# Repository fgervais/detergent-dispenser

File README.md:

# Detergent Dispenser

HE laundry detergent is quite concentrated and front loading washing machines
use really little water. With those two factors put together, it's really easy
to put too much detergent and so soap will be left even after the rinse cycle.

This project aim to automate the dispensing of a precise amount of detergent.

## Board

## Assembled Unit

After holding the button for 1 seconds, the pump will dispense 7.5ml of
detergent. This has been empirically determined to be the required amount
for a small load on our dishwasher using our usual soap.

## Installed

The pump feeds directly from the bottle.

### Resource Efficiency

The bottle in this picture is rated for 44 loads but with the proper quantity determined for our specific case along with precise dispensing, we will get over 250 loads from this bottle.

(272 small loads of 7.5ml)

## Control App (Blynk)

The app shows when a dispense occurred and keep a global count since last
manual reset. It is also possible to start a dispense from the app.

All controls are locked by default and need to get unlocked through the
lock/unlock button. Once unlocked, only a single action is allowed before
controls are locked again automatically. This is to prevent unwanted counter reset or dispense.

## Next Steps

A couple improvements could be done to this project.

1. The output of the dispenser could be permanently mounted to the washing
machine soap compartment.

2. In normal mode, the esp32 uses quite a lot of power and this translates to
a power regulator hovering just under 70C in normal operation. As the device
does nothing most of the time, power management could be added so the regulator
doesn't have to dissipate that much power.

3. The ground/power doesn't seem to be so stable on the board as touching the
pins can sometime trigger a button press or a glitch on the pump sync signal.
This doesn't seem to be too much of an issue when the device is assembled in
the case.

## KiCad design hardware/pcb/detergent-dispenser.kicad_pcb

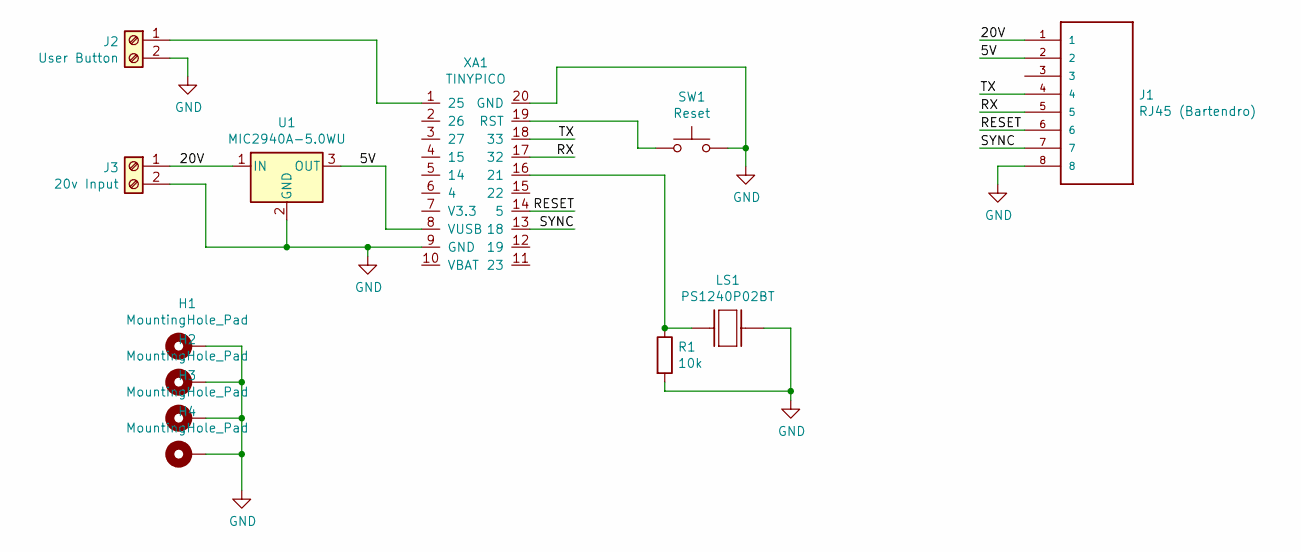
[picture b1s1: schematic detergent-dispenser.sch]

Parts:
H1, H2, H3, H4: MountingHole_Pad; MountingHole_2.7mm_M2.5_Pad
J1: RJ45 (Bartendro); AMPHENOL_RJHSE-5080
J2: User Button; TE_1546215-2
J3: 20v Input; TE_1546215-2
LS1: PS1240P02BT; XDCR_PS1240P02BT
R1: 10k; C_0603_1608Metric_Pad1.05x0.95mm_HandSolder
SW1: Reset; SW_SPST_TL3342
U1: MIC2940A-5.0WU; TO-263-3_TabPin2
XA1: TINYPICO

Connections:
/5V: J1.2, U1.3 (OUT), XA1.8 (VUSB)
/20V: J1.1, J3.1, U1.1 (IN)
/RESET: J1.6, XA1.14 (5)
/RX: J1.5, XA1.17 (32)
/SYNC: J1.7, XA1.13 (18)
/TX: J1.4, XA1.18 (33)
GND: H1.1, H2.1, H3.1, H4.1, J1.8, J2.2, J3.2, LS1.2, R1.2, SW1.2, U1.2 (GND), XA1.9 (GND), XA1.20 (GND)
unnamed: J2.1, XA1.1 (25)
unnamed: LS1.1, R1.1, XA1.16 (21)
unnamed: SW1.1, XA1.19 (RST)

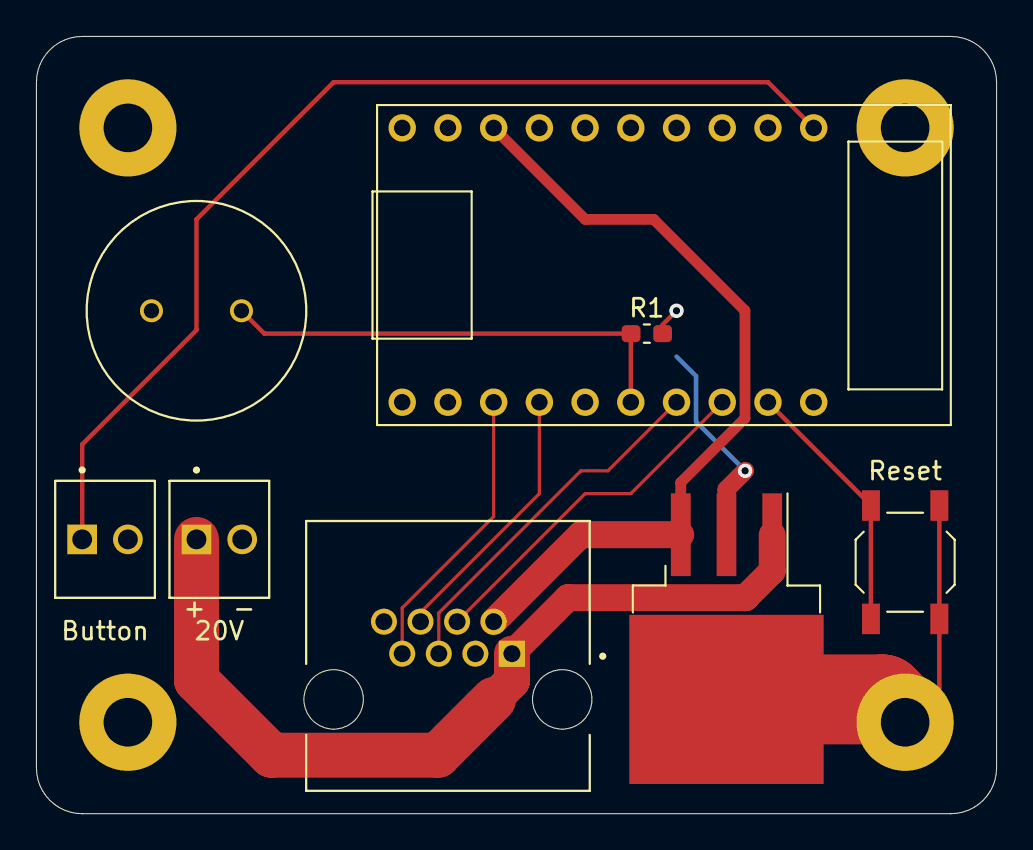
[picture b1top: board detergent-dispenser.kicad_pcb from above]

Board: 2 copper layers, 53.3 x 43.2 mm, 12 parts (0 on the bottom side), 10 nets.

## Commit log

2020-09-07 PCB rev 0
2020-09-08 Export rev 0 schematic as pdf
2020-09-08 Got the Bartendro reset and sync pin going
2020-10-12 Send the pump discovery token and add button
2020-10-12 Add initial README
2020-10-12 Detect when Bartendro is ready
2020-10-12 Add a note to PCB about 5v protection
2020-10-13 Add button IRQ
2020-10-13 Print help on button press
2020-10-15 Enter text mode in every cases
2020-11-19 Set led_done on button press
2020-11-21 Dispense outside of interrupt context
2020-11-23 Add lib-python submodule
2020-11-23 Add control over a blynk button
2020-12-10 Enable WebREPL
2020-12-10 Add upydev
2020-12-13 Add lock button handling
2020-12-13 Remove commented out code
2020-12-13 Pump only a little
2020-12-13 Use SSL
2020-12-13 Format main.py with black
2020-12-13 Remove SSL connection through proxy
2020-12-13 Sync dispense count
2020-12-13 Automatically lock controls
2020-12-13 Add counter handling
2020-12-13 Add upydev config to ignored files
2020-12-21 Use blynklib_ssl.SslConnection
2020-12-21 Early connect to wifi
    Allows connecting to the wrepl earlier.
2020-12-21 Do not use leds
2020-12-21 Add buzzer on button press
2020-12-21 Increase the dispense count correctly
2020-12-31 Add blynklib_mp_ssl.py
2020-12-31 Change to my lib-python fork
2021-01-02 Add init_tinypico.sh
2021-01-02 Need to hold the button to dispense
2021-01-03 Add the assembled unit image
2021-01-04 Adjust dispensing for soap
2021-01-04 Add information to the README
2021-01-04 Update board image
2021-01-04 Add app section
2021-01-05 Make app screenshot smaller
2021-01-05 Fix installed image caption
2021-01-06 Add a Buzzer class
2021-01-06 Use a more robust long press detection
2021-01-06 Remove code placeholder to sleep after dispense
2021-01-06 Set button as a Bartendro class member
2021-01-06 Run black
2021-01-09 Better long press handling
2021-01-09 Fix ticks_diff from time module
2021-01-09 Set dispense amount to 7.5 ml
2021-01-14 Fix blynk reconnect bug
2021-01-30 Update installed image
2021-01-30 Update App image
2023-01-10 Remove Blynk
